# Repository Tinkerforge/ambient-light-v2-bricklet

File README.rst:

Ambient Light Bricklet 2.0
==========================

This repository contains the firmware source code and the hardware design
files. The documentation generator configs can be found at
https://github.com/Tinkerforge/generators

Repository Content
------------------

software/:
 * examples/: Examples for all supported languages
 * build/: Compiled files
 * src/: Source code of firmware
 * Makefile: Makefile to build project

hardware/:
 * Contains KiCad project files and additionally schematics as PDF

datasheets/:
 * Contains datasheets for sensors and complex ICs that are used

Hardware
--------

The hardware is designed with the open source EDA Suite KiCad
(http://www.kicad.org). Before you are able to open the files,
you have to install the Tinkerforge kicad-libraries
(https://github.com/Tinkerforge/kicad-libraries). You can either clone
them directly in hardware/ or clone them in a separate folder and
symlink them into hardware/
(ln -s kicad_path/kicad-libraries project_path/hardware). After that you
can open the .pro file in hardware/ with KiCad and from there view and
modify the schematics and the PCB layout.

Software
--------

If you want to do your own Brick/Bricklet firmware development we highly
recommend that you use our build environment setup script and read the
tutorial (https://www.tinkerforge.com/en/doc/Tutorials/Tutorial_Build_Environment/Tutorial.html).

To compile the C code we recommend you to install the newest GNU Arm Embedded
Toolchain (https://launchpad.net/gcc-arm-embedded/+download).
You also need to install bricklib (https://github.com/Tinkerforge/bricklib)
and brickletlib (https://github.com/Tinkerforge/brickletlib).

You can either clone it directly in software/src/ or clone it in a
separate folder and symlink it into software/src/
(ln -s bricklib_path/bricklib project_path/software/src/ and
ln -s brickletlib_path/brickletlib project_path/software/src/).
Finally make sure to have CMake installed
(http://www.cmake.org/cmake/resources/software.html).

After that you can build the firmware by invoking make in software/.
The firmware (.bin) can then be found in software/build/ and uploaded
with brickv (click button "Flashing" on start screen).

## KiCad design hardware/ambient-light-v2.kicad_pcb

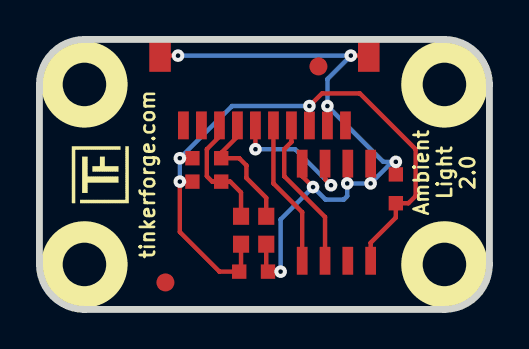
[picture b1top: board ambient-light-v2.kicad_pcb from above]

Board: 2 copper layers, 25.0 x 15.0 mm, 15 parts (2 on the bottom side), 7 nets.

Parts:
C1, C2: 100nF; C0603
Fiducial_Mark: VAL**; Fiducial_Mark
Fiducial_Mark#2: VAL**; Fiducial_Mark
P1: CON-SENSOR
R1, R2: 2k2; R0603
U1: M24C64; SOIC8
U2: LTR-329ALS
U3, U4, U5, U6: DRILL; DRILL_NP
VAL: CE_5mm
VAL#2: WEEE_7mm_back

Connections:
GND: C1.1, C2.1, P1.2, P1.EP, U1.1, U1.2, U1.4, U2.2
unnamed: P1.6, U1.3
unnamed: P1.7, R1.2, U2.3
unnamed: P1.8, R2.2, U2.4
SCL: P1.4, U1.6
SDA: P1.5, U1.5
VCC: C1.2, C2.2, P1.3, R1.1, R2.1, U1.8, U2.1

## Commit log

2015-04-02 Add readme
2015-04-02 Add LTR329 datasheet
2015-04-02 ambient light v2 prototype
2015-04-02 Add initial stub implementation of new API
2015-04-02 add fiducials
2015-04-02 order version
2015-04-02 Implement I2C communication and configuration API
2015-04-09 Add Appendix A
2015-04-09 Implement Lux formulas from Appendix A
2015-04-16 Fix display name in readme
2015-04-16 Add .gitignore
2015-04-16 Change configuration to fit production version
2015-04-23 Add Python examples
2015-04-24 drc check runned
2015-04-30 Add missing setter return
2015-05-04 Add examples for C and Python
2015-05-04 Add C# examples
2015-05-04 Add Delphi examples
2015-05-04 Add Java examples
2015-05-04 Add JavaScript examples
2015-05-04 Add Perl examples
2015-05-04 Add PHP examples
2015-05-04 Add Ruby examples
2015-05-04 Add Shell examples
2015-05-04 Add matlab/octave examples
2015-05-04 Add Mathematica examples
2015-05-05 Add VB.NET examples
2015-05-08 last_value should only be set in bricklet_simple
2015-06-18 Add LabVIEW and Mathematica examples
    Also clean up other examples.
2015-06-24 javascript: Cleanup output creation
2015-06-24 vbnet: Use correct type
2015-06-25 octave: Handle long difference between Octave 3.6 and 3.8
    In Octave 3.6 a long is not automatically handled as a number.
2015-07-16 Fix initial configuration
    INTEGRATION_TIME_* and RANGE_* are constants for the register values.
    They cannot be used for the API constants as their values don't match.
2015-07-23 Make JavaScript browser example textarea readonly
2015-07-27 Cleanup C/C++, C#, Java, Python and Ruby examples
2015-07-29 Reformat changelog
2015-07-29 Fix typo
2015-08-03 add missing schematic
2015-08-07 Use full device class name in Python examples
2015-08-11 Completely ignore invalid values
    Before, the code assumed that a meaningful lux value could still be
    deduced from invalid sensor values. This is not the case. It seems that
    the invalid flag indicates an internal value overflow or saturation
    in the sensor, which might come from a too high gain or a too long
    integration time. In both cases one or both ADC values are wrong and
    cannot be used.
2015-08-12 Fix minor warnings in C/C++ examples
2015-08-14 Cleanup Delphi examples
2015-08-17 Update changelog
2015-08-18 Cleanup VB.NET examples
2015-08-19 Cleanup Perl examples
2015-08-21 Prefer printf over puts in C/C++ examples
2015-09-10 Duplicate cmake call to fix bug during cmake creation
    Also, toolchain is now in bricklib.
2015-09-16 Improve user-experience in saturation and out-of-range situations
2015-09-30 Generator based example cleanup
2015-11-12 matlab: Fix callback handling for R2014a
    http://undocumentedmatlab.com/blog/matlab-callbacks-for-java-events-in-r2014a
2015-11-25 Include date and commit into changelog
2015-11-30 vbnet: Break long line
2016-02-18 updated silkscreen
2016-04-06 add pin1 mark to sensor ic
2016-05-18 c: Add missing device destroy call
2016-06-29 Whitespace
2016-07-01 Make the change UID comment more explicit
2017-04-13 csharp: Adapt example
2017-04-21 shell: Adapt example
2017-06-02 octave: Use javaObject instead of deprecated java_new
2017-08-01 Add 3d information (final)
2017-08-01 Add 3d model (*.step & *.FCStd)
2017-11-30 Update examples from generator
2017-12-07 mathematica: Also generate .nb files
2018-01-30 Update examples
2018-02-19 javascript: Close div tag correctly
2018-02-20 Cleanup KiCad libraries config
    Ensure LibDir=kicad-libraries and LibName1=tinkerforge.
    Remove special library.
2018-05-11 Rename file
2018-05-11 Rename files
2018-05-24 perl: Use strict in examples
2018-07-11 Add Makefile with docker support
2018-07-11 Remove obsolete generate_makefile scripts
2018-07-11 Update directory structure and build instructions
2018-11-06 Add rust examples
2018-11-07 rust: Accept host names for ip connection, fix naming inconsistencies
2018-11-07 rust: Rename callback receivers.
2018-12-14 Add go examples.
2018-12-14 go: Fix printf parameters.
2018-12-18 go: Change import path.
2018-12-18 go: Change import path again.
2018-12-20 rust: Reformat examples.
2019-01-24 mqtt: Add examples.
2019-01-24 mqtt: Fix example header.
2019-01-24 mqtt: Remove executable bit in example permissions.
2019-01-24 go: Minor example fixes.
2019-01-24 mqtt: Minor example fixes.
2019-03-28 mqtt: Fix whitespace.
2019-08-22 c: Adapt to bindings changes
2020-01-13 examples: Use python3 input instead of python2 raw_input.
2020-01-13 examples: mqtt: Remove trailing whitespace.
2020-04-13 Fixed wrong bricklet name in treshold example
2021-10-25 Update KiCad link
    https://www.kicad.org/blog/2021/10/Avoid-links-to-former-kicad-domain/
2022-07-06 Add license files.

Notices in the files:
hardware/ambient-light-v2.kicad_pcb:
Licensed under CERN OHL v.1.1
Copyright (©) 2015, B.Nordmeyer
Copyright Tinkerforge GmbH 2015.
This documentation describes Open Hardware and is licensed under the
CERN OHL v. 1.1.
